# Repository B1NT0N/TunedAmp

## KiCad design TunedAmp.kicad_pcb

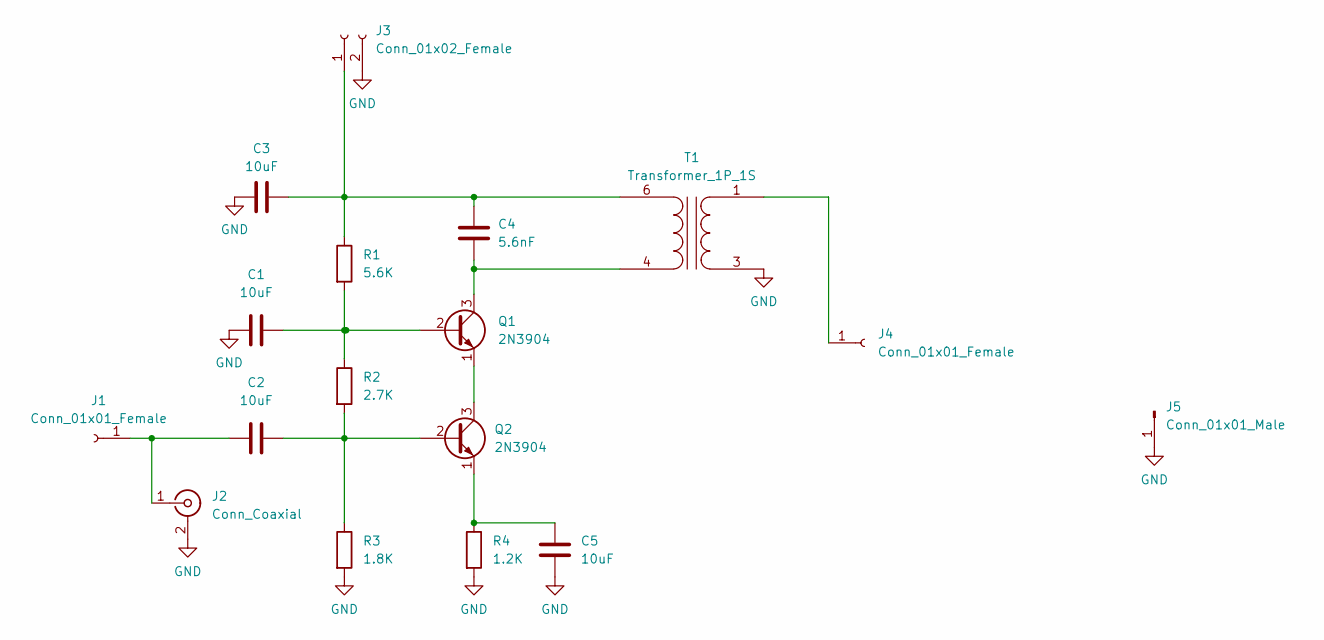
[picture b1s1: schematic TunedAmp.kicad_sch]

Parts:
C1, C2, C3, C5: 10uF; CP_Radial_D5.0mm_P2.00mm
C4: 5.6nF; C_Disc_D7.5mm_W2.5mm_P5.00mm
J1, J4: Conn_01x01_Female; PinSocket_1x01_P2.00mm_Vertical
J2: Conn_Coaxial; SMA_Molex_73251-2200_Horizontal
J3: Conn_01x02_Female; JST_XH_B2B-XH-A_1x02_P2.50mm_Vertical
J5: Conn_01x01_Male; PinHeader_1x01_P1.00mm_Vertical
Q1, Q2: 2N3904; TO-92_Inline
R1: 5.6K; R_Axial_DIN0207_L6.3mm_D2.5mm_P7.62mm_Horizontal
R2: 2.7K; R_Axial_DIN0207_L6.3mm_D2.5mm_P7.62mm_Horizontal
R3: 1.8K; R_Axial_DIN0207_L6.3mm_D2.5mm_P7.62mm_Horizontal
R4: 1.2K; R_Axial_DIN0207_L6.3mm_D2.5mm_P7.62mm_Horizontal
T1: Transformer_1P_1S; Transformer_NF_ETAL_1-1_P1200

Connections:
GND: C1.2, C3.2, C5.2, J2.2 (Ext), J3.2, J5.1, R3.2, R4.2, T1.3 (SA)
unnamed: C2.1, J1.1, J2.1 (In)
unnamed: C4.1, Q1.3 (C), T1.4 (AB)
unnamed: C3.1, C4.2, J3.1, R1.1, T1.6 (AA)
unnamed: J4.1, T1.1 (SB)
unnamed: Q1.1 (E), Q2.3 (C)
unnamed: C1.1, Q1.2 (B), R1.2, R2.1
unnamed: C5.1, Q2.1 (E), R4.1
unnamed: C2.2, Q2.2 (B), R2.2, R3.1

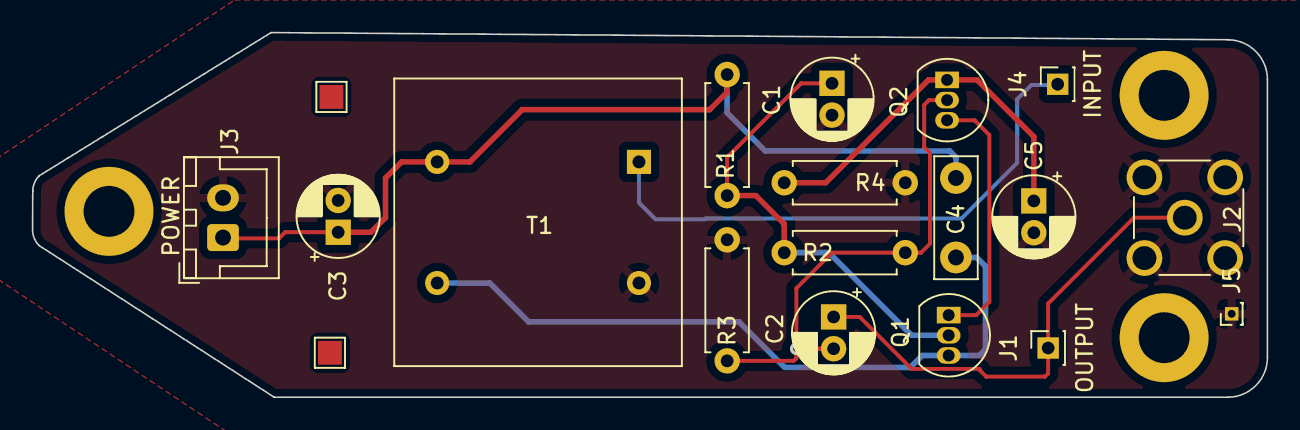
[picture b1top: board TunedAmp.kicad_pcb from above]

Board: 2 copper layers, 77.7 x 23.0 mm, 17 parts (0 on the bottom side), 9 nets.

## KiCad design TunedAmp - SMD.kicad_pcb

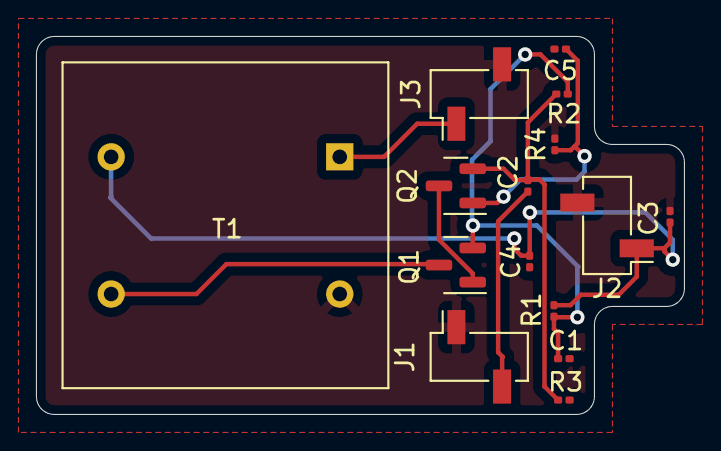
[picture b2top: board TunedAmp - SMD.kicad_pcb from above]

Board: 2 copper layers, 36.0 x 21.0 mm, 15 parts (0 on the bottom side), 9 nets.

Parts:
C1, C2, C3, C5: 10uF; C_0201_0603Metric
C4: 5.6nF; C_0201_0603Metric
J1: Conn_01x02_Female; PinSocket_1x02_P2.54mm_Vertical_SMD_Pin1Right
J2, J3: Conn_01x02_Female; PinSocket_1x02_P2.54mm_Vertical_SMD_Pin1Left
Q1, Q2: 2N3904; SOT-23
R1: 5.6K; R_0201_0603Metric
R2: 2.7K; R_0201_0603Metric
R3: 1.8K; R_0201_0603Metric
R4: 1.2K; R_0201_0603Metric
T1: Transformer_1P_1S; Transformer_NF_ETAL_1-1_P1200

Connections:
GND: C1.1, C3.1, C5.1, J1.1, J2.2, J3.2, R3.2, R4.2, T1.3 (SA)
unnamed: C1.2, Q1.2 (B), R1.2, R2.1
unnamed: C2.1, J1.2
unnamed: C2.2, Q2.2 (B), R2.2, R3.1
unnamed: C3.2, C4.2, J2.1, R1.1, T1.6 (AA)
unnamed: C4.1, Q1.3 (C), T1.4 (AB)
unnamed: C5.2, Q2.1 (E), R4.1
unnamed: J3.1, T1.1 (SB)
unnamed: Q1.1 (E), Q2.3 (C)
